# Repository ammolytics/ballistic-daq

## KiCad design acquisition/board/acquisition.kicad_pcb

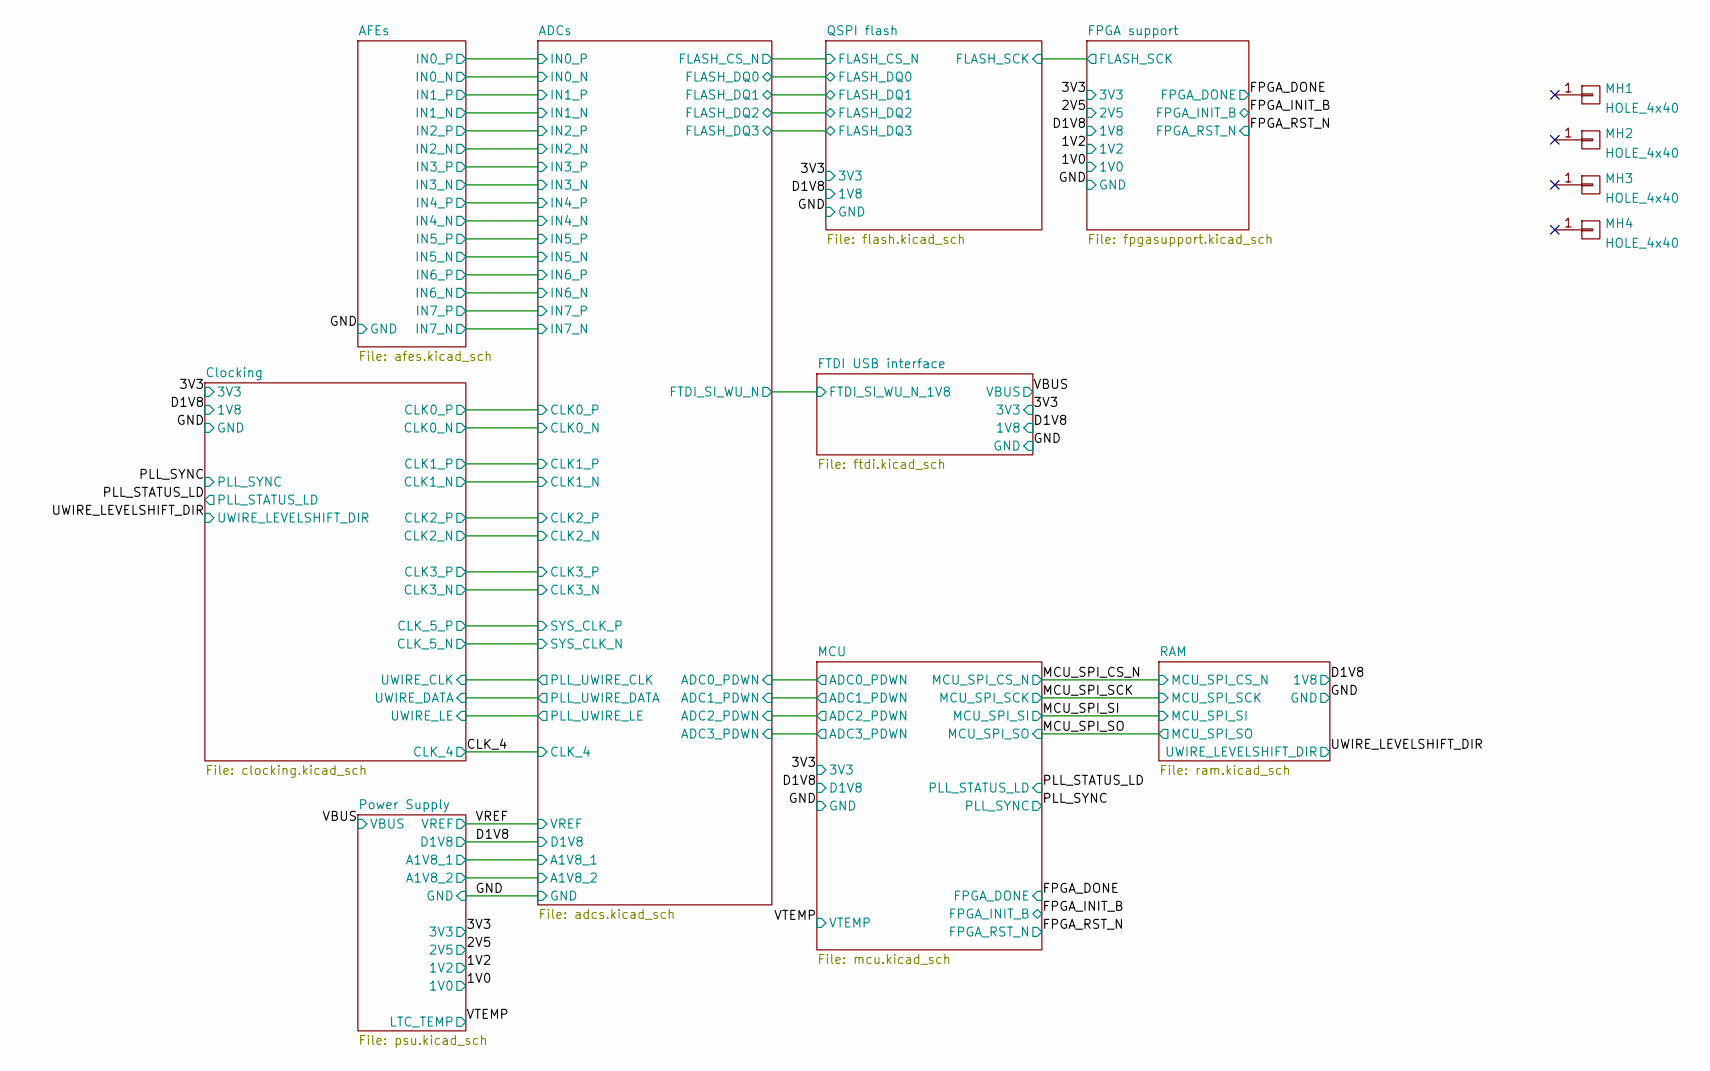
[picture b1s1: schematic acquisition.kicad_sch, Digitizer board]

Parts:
MH1, MH2, MH3, MH4: HOLE_4x40; MECHANICAL_CLEARANCEHOLE_4_40

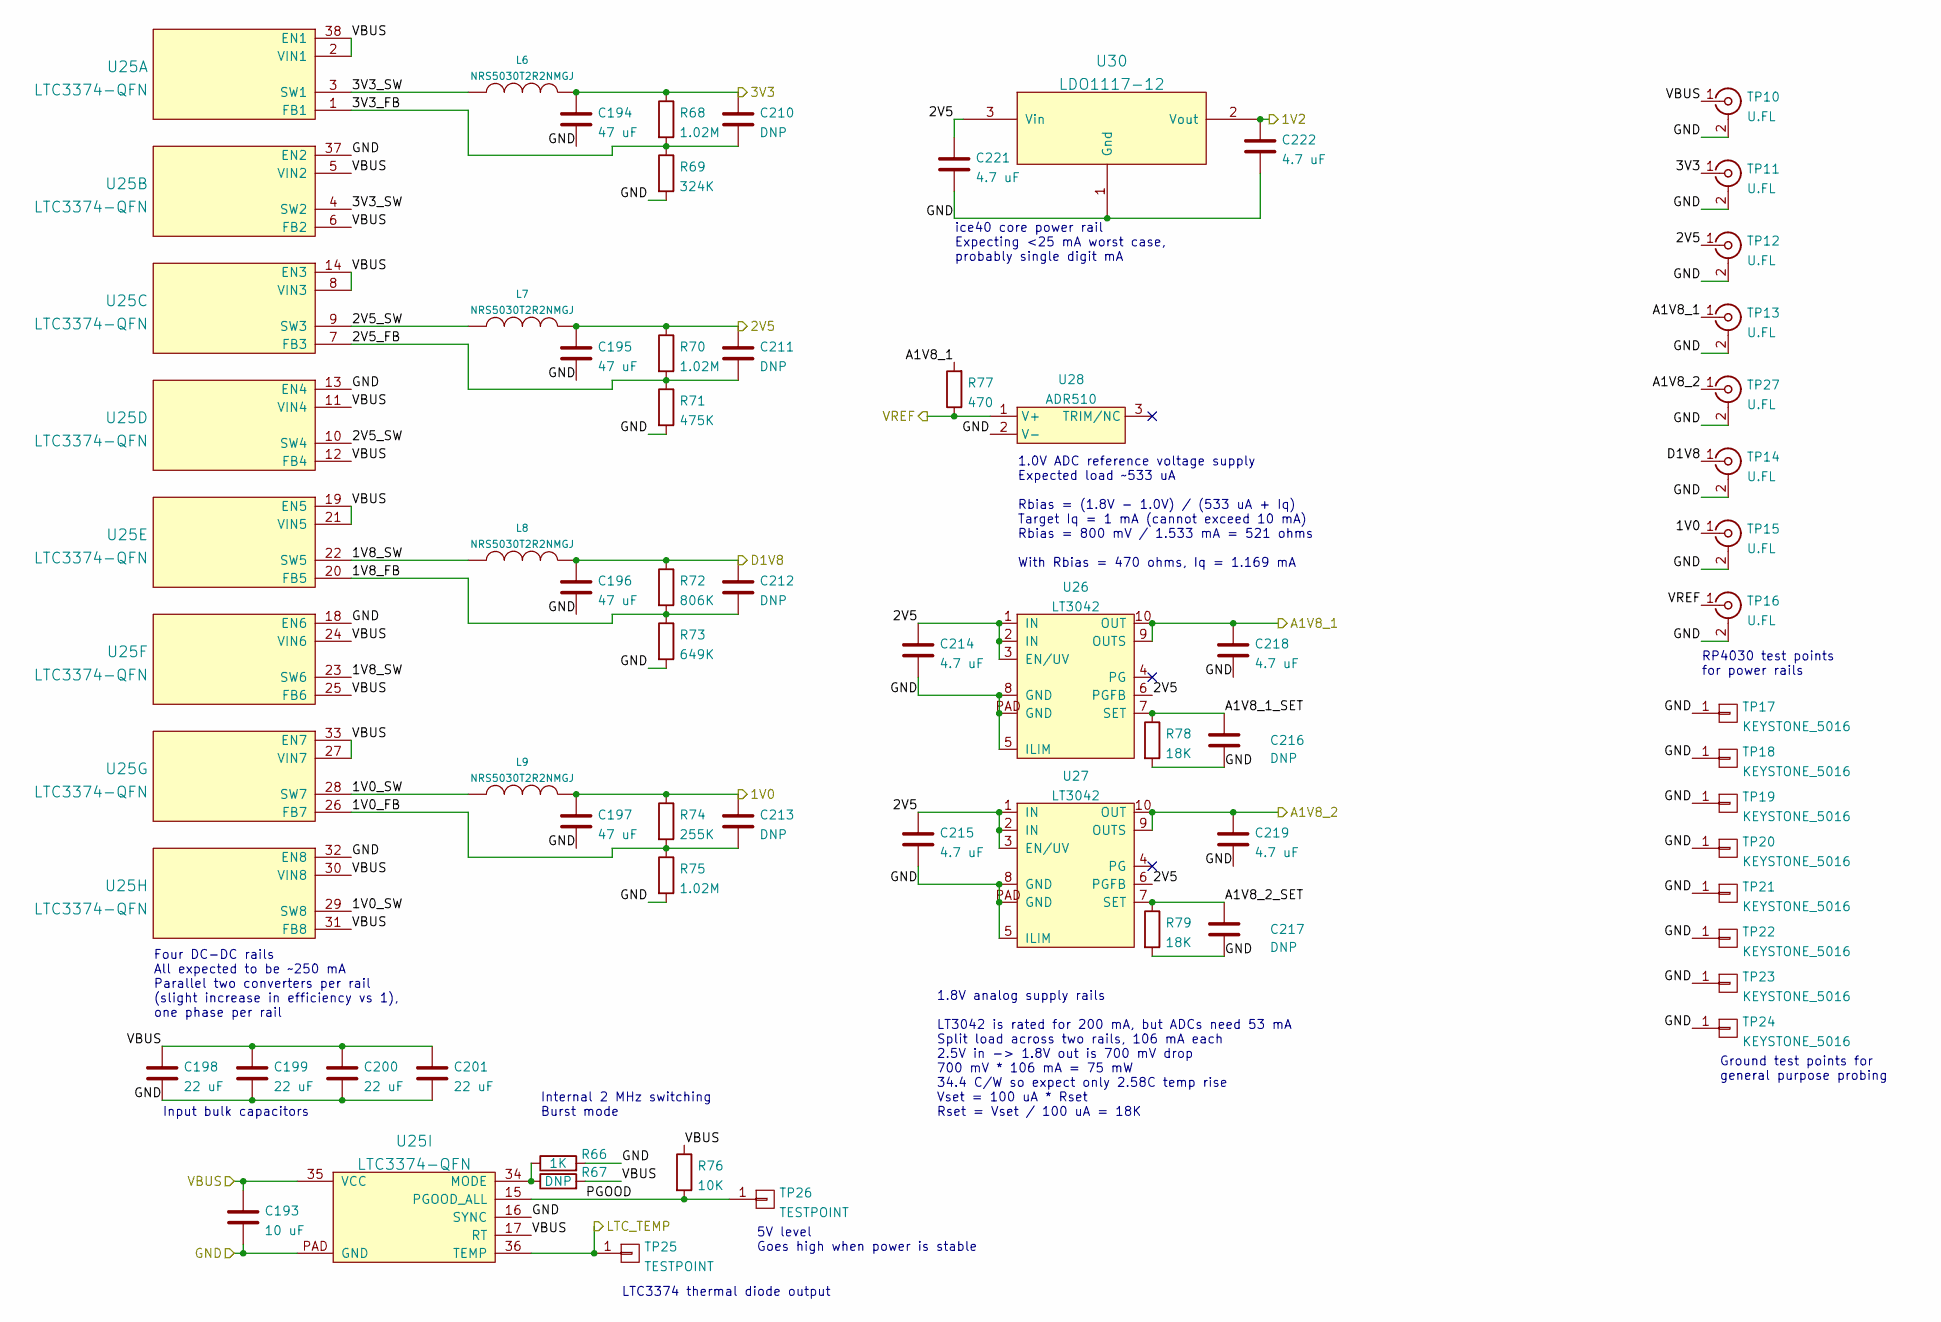
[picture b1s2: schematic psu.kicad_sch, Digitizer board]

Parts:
C193: 10 uF; EIA_1206_CAP_NOSILK
C194, C195, C196, C197: 47 uF; EIA_1206_CAP_NOSILK
C198, C199, C200, C201: 22 uF; EIA_1210_CAP_NOSILK
C210, C211, C212, C213, C216, C217: DNP; EIA_0402_CAP_NOSILK
C214, C215, C218, C219, C221, C222: 4.7 uF; EIA_0603_CAP_NOSILK
L6, L7, L8, L9: NRS5030T2R2NMGJ; INDUCTOR_YUDEN_NRS5030
R66: 1K; EIA_0402_RES_NOSILK
R67: DNP; EIA_0402_RES_NOSILK
R68, R70, R75: 1.02M; EIA_0402_RES_NOSILK
R69: 324K; EIA_0402_RES_NOSILK
R71: 475K; EIA_0402_RES_NOSILK
R72: 806K; EIA_0402_RES_NOSILK
R73: 649K; EIA_0402_RES_NOSILK
R74: 255K; EIA_0402_RES_NOSILK
R76: 10K; EIA_0402_RES_NOSILK
R77: 470; EIA_0402_RES_NOSILK
R78, R79: 18K; EIA_0402_RES_NOSILK
TP10, TP11, TP12, TP13, TP14, TP15, TP16, TP27: U.FL; CONN_U.FL_TE_1909763-1
TP17, TP18, TP19, TP20, TP21, TP22, TP23, TP24: KEYSTONE_5016; TESTPOINT_SMT_KEYSTONE_5016
TP25, TP26: TESTPOINT; TESTPOINT_SMT_0.5MM
U25: LTC3374-QFN; QFN_38_0.5MM_5x7MM
U26, U27: LT3042; DFN_10_0.5MM_3x3MM
U28: ADR510; SOT23_3
U30: LDO1117-12; SOT223-4

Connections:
/1V0: C197.1, C213.1, L9.1, R74.1, TP15.1 (In); also elsewhere on the board
/1V2: C222.1, U30.2 (Vout); also elsewhere on the board
/2V5: C195.1, C211.1, C214.1, C215.1, C221.1, L7.1, R70.1, TP12.1 (In), U26.1 (IN), U26.2 (IN), U26.3 (EN/UV), U26.6 (PGFB), U27.1 (IN), U27.2 (IN), U27.3 (EN/UV), U27.6 (PGFB), U30.3 (Vin); also elsewhere on the board
/3V3: C194.1, C210.1, L6.1, R68.1, TP11.1 (In); also elsewhere on the board
/ADCs/A1V8_1: C218.1, R77.2, TP13.1 (In), U26.9 (OUTS), U26.10 (OUT); also elsewhere on the board
/ADCs/A1V8_2: C219.1, TP27.1 (In), U27.9 (OUTS), U27.10 (OUT); also elsewhere on the board
/D1V8: C196.1, C212.1, L8.1, R72.1, TP14.1 (In); also elsewhere on the board
/GND: C193.2, C194.2, C195.2, C196.2, C197.2, C198.2, C199.2, C200.2, C201.2, C214.2, C215.2, C216.2, C217.2, C218.2, C219.2, C221.2, C222.2, R66.2, R69.2, R71.2, R73.2, R75.2, R78.2, R79.2, TP10.2 (Ext), TP11.2 (Ext), TP12.2 (Ext), TP13.2 (Ext), TP14.2 (Ext), TP15.2 (Ext), TP16.2 (Ext), TP17.1, TP18.1, TP19.1, TP20.1, TP21.1, TP22.1, TP23.1, TP24.1, TP27.2 (Ext), U25.13 (EN4), U25.16 (SYNC), U25.18 (EN6), U25.32 (EN8), U25.37 (EN2), U25.PAD (GND), U26.5 (ILIM), U26.8 (GND), U26.PAD (GND), U27.5 (ILIM), U27.8 (GND), U27.PAD (GND), U28.2 (V-), U30.1 (Gnd); also elsewhere on the board
/Power Supply/1V0_FB: C213.2, R74.2, R75.1, U25.26 (FB7)
/Power Supply/1V0_SW: L9.2, U25.28 (SW7), U25.29 (SW8)
/Power Supply/1V8_FB: C212.2, R72.2, R73.1, U25.20 (FB5)
/Power Supply/1V8_SW: L8.2, U25.22 (SW5), U25.23 (SW6)
/Power Supply/2V5_FB: C211.2, R70.2, R71.1, U25.7 (FB3)
/Power Supply/2V5_SW: L7.2, U25.9 (SW3), U25.10 (SW4)
/Power Supply/3V3_FB: C210.2, R68.2, R69.1, U25.1 (FB1)
/Power Supply/3V3_SW: L6.2, U25.3 (SW1), U25.4 (SW2)
/Power Supply/A1V8_1_SET: C216.1, R78.1, U26.7 (SET)
/Power Supply/A1V8_2_SET: C217.1, R79.1, U27.7 (SET)
/Power Supply/PGOOD: R76.2, TP26.1, U25.15 (PGOOD_ALL)
/VBUS: C193.1, C198.1, C199.1, C200.1, C201.1, R67.2, R76.1, TP10.1 (In), U25.2 (VIN1), U25.5 (VIN2), U25.6 (FB2), U25.8 (VIN3), U25.11 (VIN4), U25.12 (FB4), U25.14 (EN3), U25.17 (RT), U25.19 (EN5), U25.21 (VIN5), U25.24 (VIN6), U25.25 (FB6), U25.27 (VIN7), U25.30 (VIN8), U25.31 (FB8), U25.33 (EN7), U25.35 (VCC), U25.38 (EN1); also elsewhere on the board
/VREF: R77.1, TP16.1 (In), U28.1 (V+); also elsewhere on the board
/VTEMP: TP25.1, U25.36 (TEMP); also elsewhere on the board
unnamed: R66.1, R67.1, U25.34 (MODE)

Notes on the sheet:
ice40 core power rail Expecting <25 mA worst case, probably single digit mA
LTC3374 thermal diode output
Ground test points for general purpose probing
5V level Goes high when power is stable
Input bulk capacitors
1.8V analog supply rails LT3042 is rated for 200 mA, but ADCs need 53 mA Split load across two rails, 106 mA each 2.5V in -> 1.8V out is 700 mV drop 700 mV * 106 mA = 75 mW 34.4 C/W so expect only 2.58C temp rise Vset = 100 uA * Rset Rset = Vset / 100 uA = 18K
Internal 2 MHz switching Burst mode
RP4030 test points for power rails
Four DC-DC rails All expected to be ~250 mA Parallel two converters per rail (slight increase in efficiency vs 1), one phase per rail
1.0V ADC reference voltage supply Expected load ~533 uA Rbias = (1.8V - 1.0V) / (533 uA + Iq) Target Iq = 1 mA (cannot exceed 10 mA) Rbias = 800 mV / 1.533 mA = 521 ohms With Rbias = 470 ohms, Iq = 1.169 mA

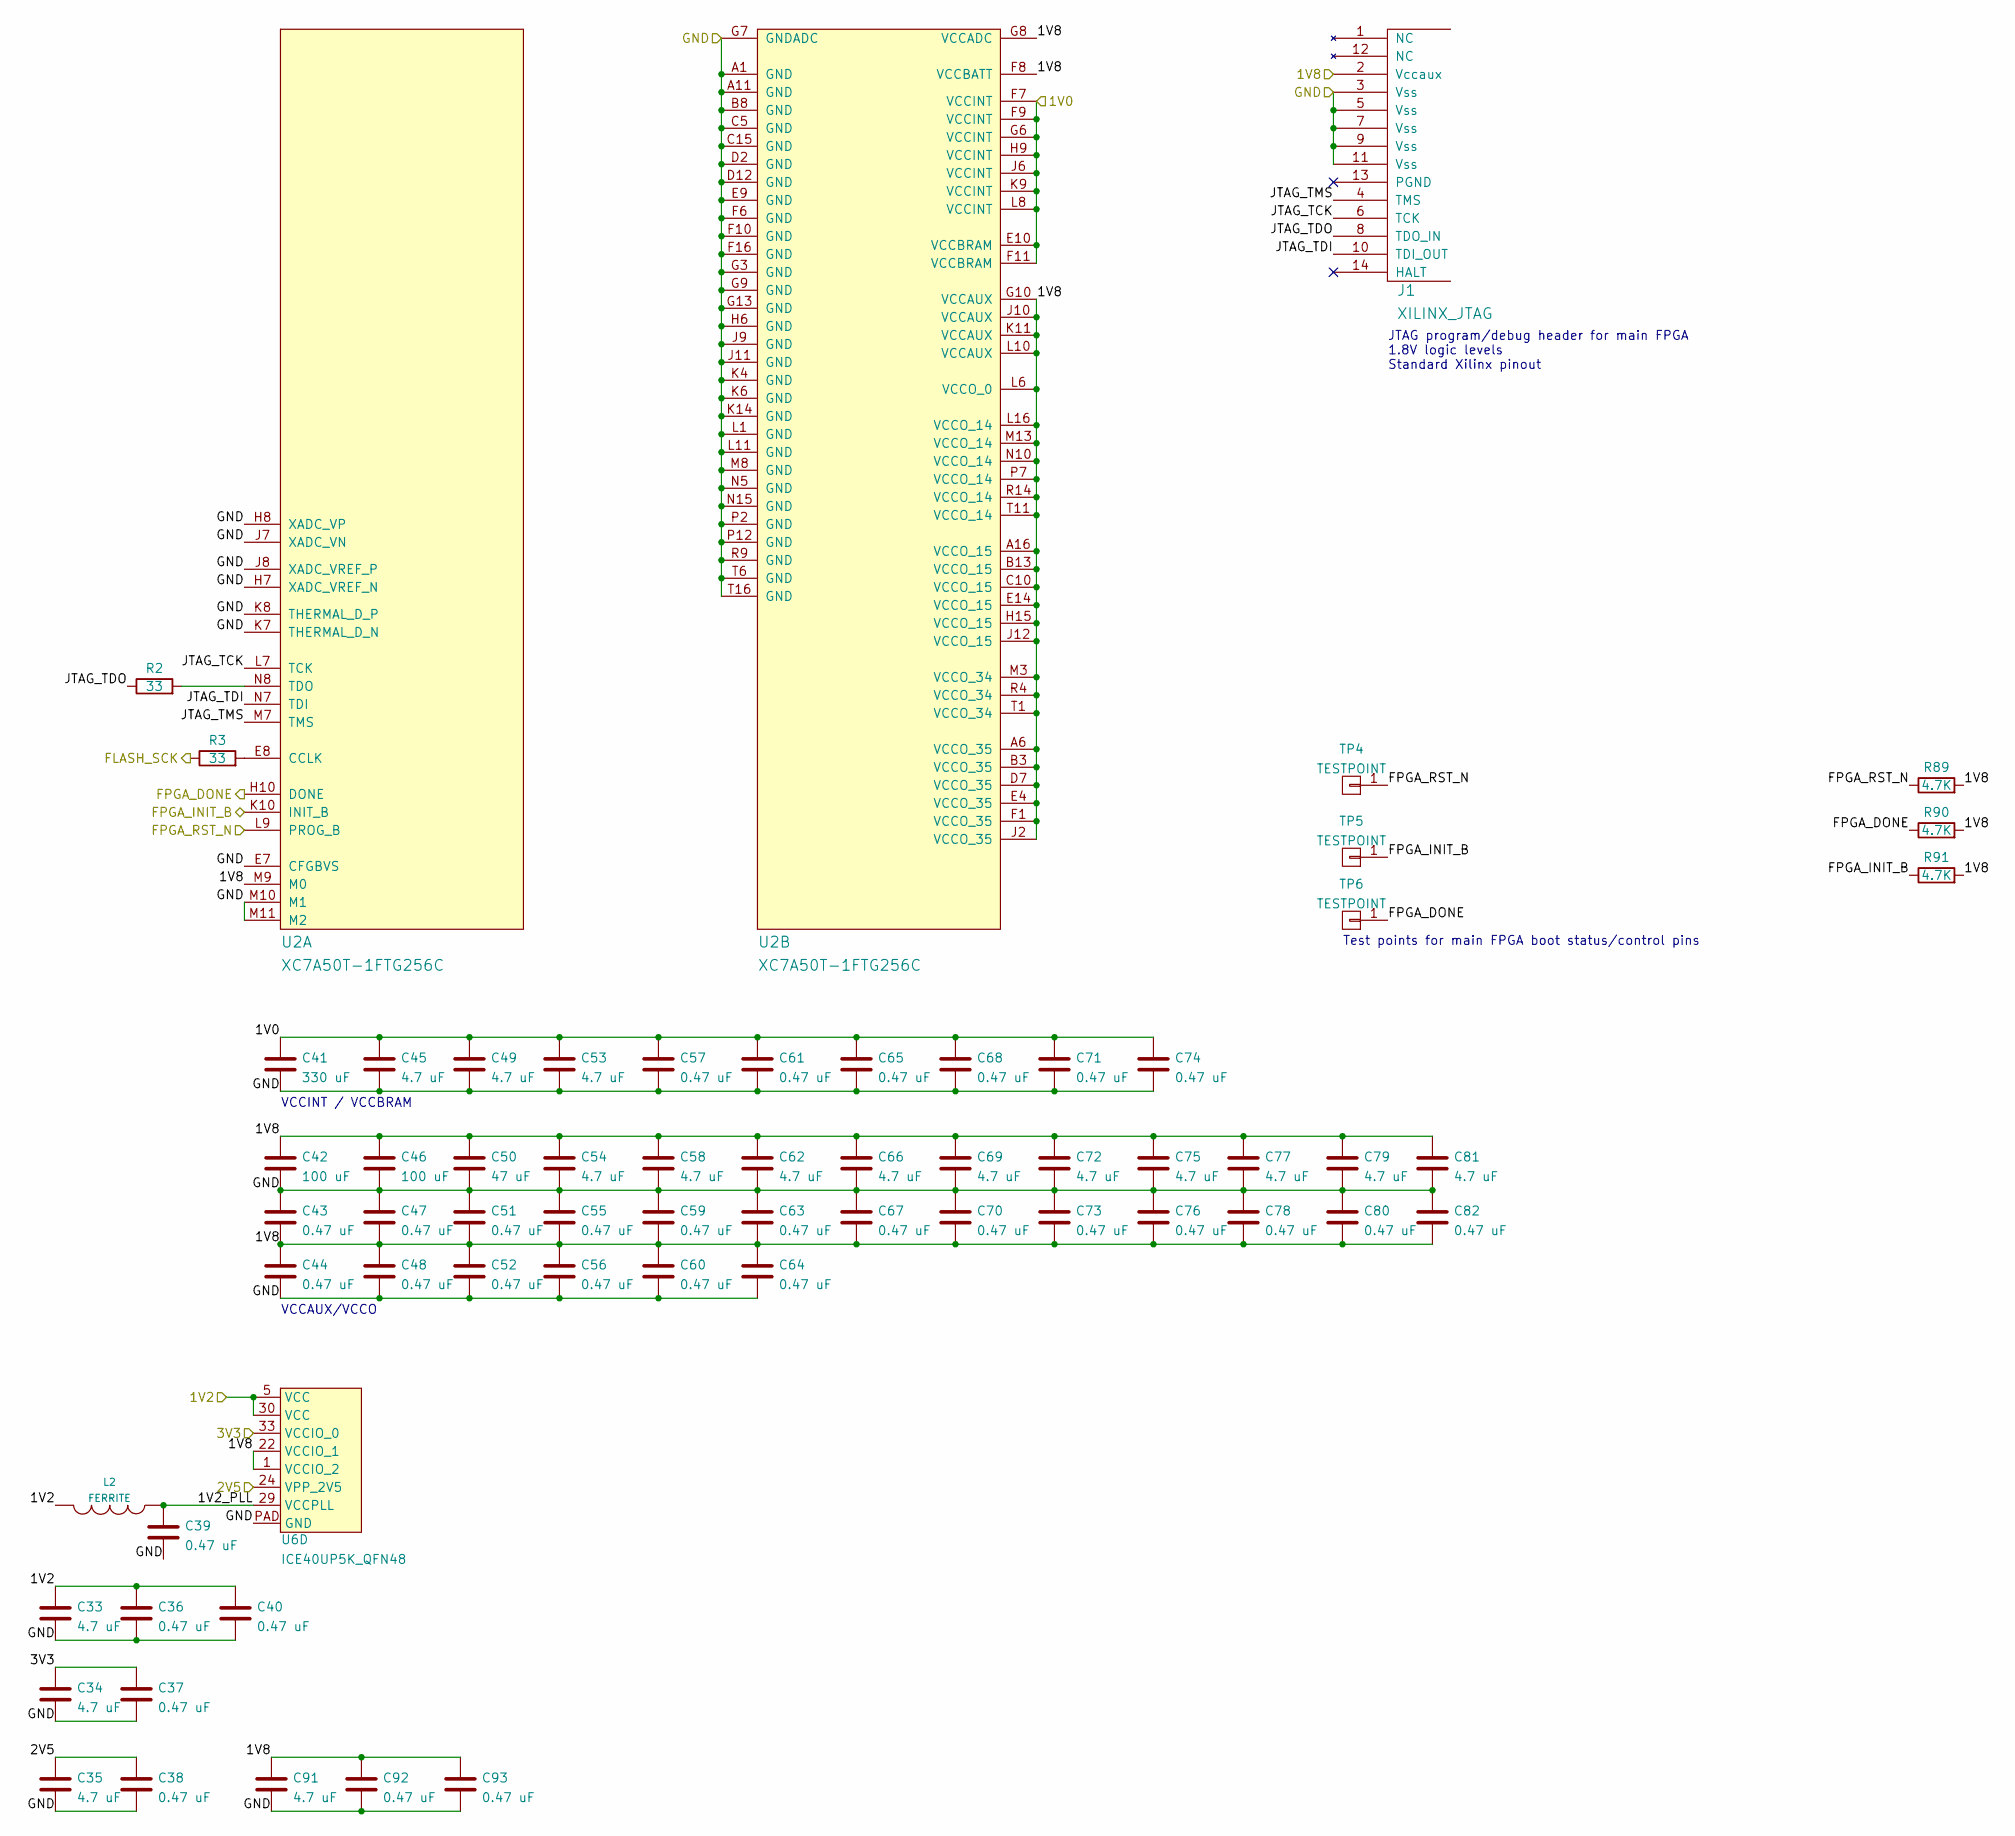
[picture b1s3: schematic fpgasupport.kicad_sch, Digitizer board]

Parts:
C33, C34, C35, C45, C49, C53, C54, C58, C62, C66, C69, C72, C75, C77, C79, C81, C91: 4.7 uF; EIA_0603_CAP_NOSILK
C36, C37, C38, C39, C40, C43, C44, C47, C48, C51, C52, C55, C56, C57, C59, C60, C61, C63, C64, C65, C67, C68, C70, C71, C73, C74, C76, C78, C80, C82, C92, C93: 0.47 uF; EIA_0402_CAP_NOSILK
C41: 330 uF; EIA_1210_CAP_NOSILK
C42, C46: 100 uF; EIA_1206_CAP_NOSILK
C50: 47 uF; EIA_1210_CAP_NOSILK
J1: XILINX_JTAG; XILINX_JTAG_PTH_MOLEX_0878311420
L2: FERRITE; EIA_0603_INDUCTOR_NOSILK
R2, R3: 33; EIA_0402_RES_NOSILK
R89, R90, R91: 4.7K; EIA_0402_RES_NOSILK
TP4, TP5, TP6: TESTPOINT; TESTPOINT_SMT_0.5MM
U2: XC7A50T-1FTG256C; BGA_256_17x17_FULLARRAY_1MM_0.4MM_FTG256
U6: ICE40UP5K_QFN48; QFN_48_0.5MM_7x7MM

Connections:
/1V0: C41.1, C45.1, C49.1, C53.1, C57.1, C61.1, C65.1, C68.1, C71.1, C74.1, U2.E10 (VCCBRAM), U2.F7 (VCCINT), U2.F9 (VCCINT), U2.F11 (VCCBRAM), U2.G6 (VCCINT), U2.H9 (VCCINT), U2.J6 (VCCINT), U2.K9 (VCCINT), U2.L8 (VCCINT); also elsewhere on the board
/1V2: C33.1, C36.1, C40.1, L2.2, U6.5 (VCC), U6.30 (VCC); also elsewhere on the board
/2V5: C35.1, C38.1, U6.24 (VPP_2V5); also elsewhere on the board
/3V3: C34.1, C37.1, U6.33 (VCCIO_0); also elsewhere on the board
/D1V8: C42.1, C43.2, C44.1, C46.1, C47.2, C48.1, C50.1, C51.2, C52.1, C54.1, C55.2, C56.1, C58.1, C59.2, C60.1, C62.1, C63.2, C64.1, C66.1, C67.2, C69.1, C70.2, C72.1, C73.2, C75.1, C76.2, C77.1, C78.2, C79.1, C80.2, C81.1, C82.2, C91.1, C92.1, C93.1, J1.2 (Vccaux), R89.2, R90.2, R91.2, U2.A6 (VCCO_35), U2.A16 (VCCO_15), U2.B3 (VCCO_35), U2.B13 (VCCO_15), U2.C10 (VCCO_15), U2.D7 (VCCO_35), U2.E4 (VCCO_35), U2.E14 (VCCO_15), U2.F1 (VCCO_35), U2.F8 (VCCBATT), U2.G8 (VCCADC), U2.G10 (VCCAUX), U2.H15 (VCCO_15), U2.J2 (VCCO_35), U2.J10 (VCCAUX), U2.J12 (VCCO_15), U2.K11 (VCCAUX), U2.L6 (VCCO_0), U2.L10 (VCCAUX), U2.L16 (VCCO_14), U2.M3 (VCCO_34), U2.M9 (M0), U2.M13 (VCCO_14), U2.N10 (VCCO_14), U2.P7 (VCCO_14), U2.R4 (VCCO_34), U2.R14 (VCCO_14), U2.T1 (VCCO_34), U2.T11 (VCCO_14), U6.1 (VCCIO_2), U6.22 (VCCIO_1); also elsewhere on the board
/FPGA support/1V2_PLL: C39.1, L2.1, U6.29 (VCCPLL)
/FPGA support/FLASH_SCK: R3.1; also elsewhere on the board
/FPGA support/JTAG_TCK: J1.6 (TCK), U2.L7 (TCK)
/FPGA support/JTAG_TDI: J1.10 (TDI_OUT), U2.N7 (TDI)
/FPGA support/JTAG_TDO: J1.8 (TDO_IN), R2.1
/FPGA support/JTAG_TMS: J1.4 (TMS), U2.M7 (TMS)
/FPGA_DONE: R90.1, TP6.1, U2.H10 (DONE); also elsewhere on the board
/FPGA_INIT_B: R91.1, TP5.1, U2.K10 (INIT_B); also elsewhere on the board
/FPGA_RST_N: R89.1, TP4.1, U2.L9 (PROG_B); also elsewhere on the board
/GND: C33.2, C34.2, C35.2, C36.2, C37.2, C38.2, C39.2, C40.2, C41.2, C42.2, C43.1, C44.2, C45.2, C46.2, C47.1, C48.2, C49.2, C50.2, C51.1, C52.2, C53.2, C54.2, C55.1, C56.2, C57.2, C58.2, C59.1, C60.2, C61.2, C62.2, C63.1, C64.2, C65.2, C66.2, C67.1, C68.2, C69.2, C70.1, C71.2, C72.2, C73.1, C74.2, C75.2, C76.1, C77.2, C78.1, C79.2, C80.1, C81.2, C82.1, C91.2, C92.2, C93.2, J1.3 (Vss), J1.5 (Vss), J1.7 (Vss), J1.9 (Vss), J1.11 (Vss), U2.A1 (GND), U2.A11 (GND), U2.B8 (GND), U2.C5 (GND), U2.C15 (GND), U2.D2 (GND), U2.D12 (GND), U2.E7 (CFGBVS), U2.E9 (GND), U2.F6 (GND), U2.F10 (GND), U2.F16 (GND), U2.G3 (GND), U2.G7 (GNDADC), U2.G9 (GND), U2.G13 (GND), U2.H6 (GND), U2.H7 (XADC_VREF_N), U2.H8 (XADC_VP), U2.J7 (XADC_VN), U2.J8 (XADC_VREF_P), U2.J9 (GND), U2.J11 (GND), U2.K4 (GND), U2.K6 (GND), U2.K7 (THERMAL_D_N), U2.K8 (THERMAL_D_P), U2.K14 (GND), U2.L1 (GND), U2.L11 (GND), U2.M8 (GND), U2.M10 (M1), U2.M11 (M2), U2.N5 (GND), U2.N15 (GND), U2.P2 (GND), U2.P12 (GND), U2.R9 (GND), U2.T6 (GND), U2.T16 (GND), U6.PAD (GND); also elsewhere on the board
unnamed: R2.2, U2.N8 (TDO)
unnamed: R3.2, U2.E8 (CCLK)

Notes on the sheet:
JTAG program/debug header for main FPGA 1.8V logic levels Standard Xilinx pinout
Test points for main FPGA boot status/control pins
VCCINT / VCCBRAM
VCCAUX/VCCO

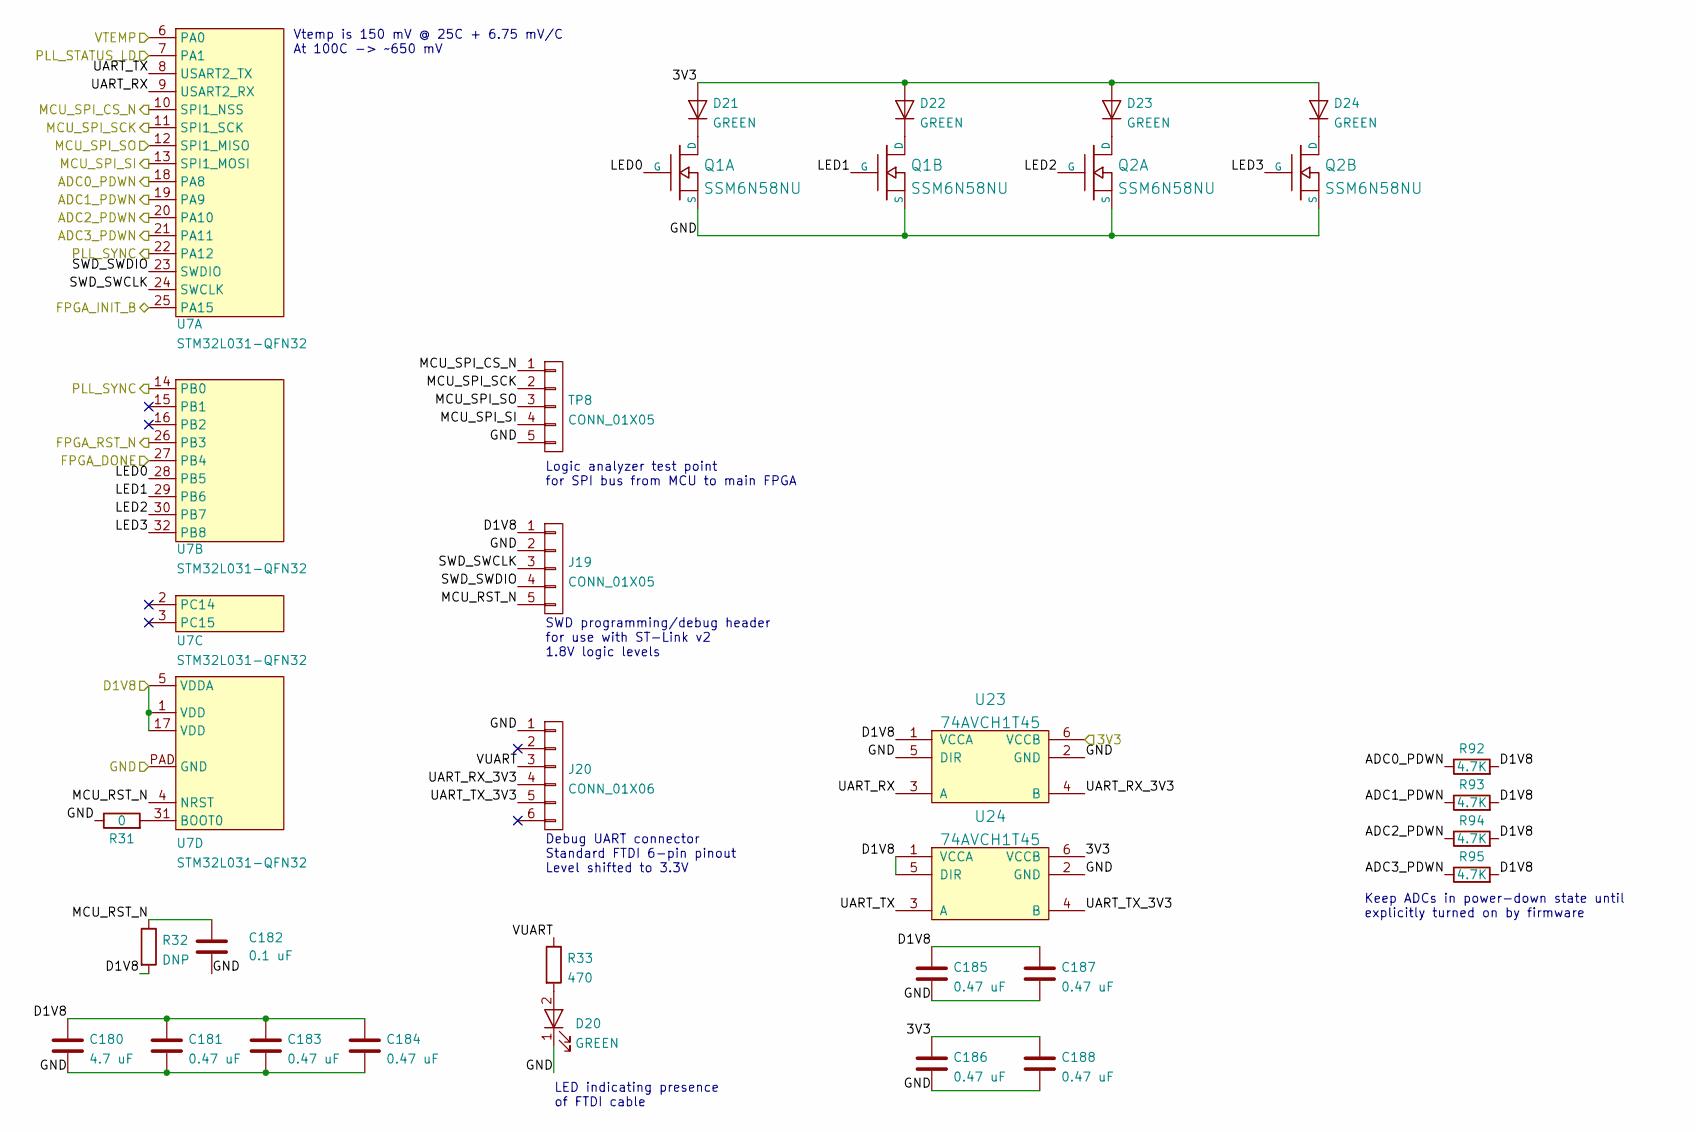
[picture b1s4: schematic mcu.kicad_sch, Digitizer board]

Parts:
C180: 4.7 uF; EIA_0603_CAP_NOSILK
C181, C183, C184, C185, C186, C187, C188: 0.47 uF; EIA_0402_CAP_NOSILK
C182: 0.1 uF; EIA_0402_CAP_NOSILK
D20, D21, D22, D23, D24: GREEN; EIA_0603_LED
J19: CONN_01X05; CONN_HEADER_2.54MM_1x5
J20: CONN_01X06; CONN_HEADER_2.54MM_1x6
Q1, Q2: SSM6N58NU; DFN_6_0.65MM_2x2MM_GDS
R31: 0; EIA_0402_RES_NOSILK
R32: DNP; EIA_0402_RES_NOSILK
R33: 470; EIA_0402_RES_NOSILK
R92, R93, R94, R95: 4.7K; EIA_0402_RES_NOSILK
TP8: CONN_01X05; CONN_HEADER_2.54MM_1x5
U7: STM32L031-QFN32; QFN_32_0.5MM_5x5MM
U23, U24: 74AVCH1T45; DFN_6_0.5MM_1.45x1.00MM

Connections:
/3V3: C186.1, C188.1, D21.2 (A), D22.2 (A), D23.2 (A), D24.2 (A), U23.6 (VCCB), U24.6 (VCCB); also elsewhere on the board
/D1V8: C180.1, C181.1, C183.1, C184.1, C185.1, C187.1, J19.1, R32.2, R92.2, R93.2, R94.2, R95.2, U7.1 (VDD), U7.5 (VDDA), U7.17 (VDD), U23.1 (VCCA), U24.1 (VCCA), U24.5 (DIR); also elsewhere on the board
/FPGA_DONE: U7.27 (PB4); also elsewhere on the board
/FPGA_INIT_B: U7.25 (PA15); also elsewhere on the board
/FPGA_RST_N: U7.26 (PB3); also elsewhere on the board
/GND: C180.2, C181.2, C182.2, C183.2, C184.2, C185.2, C186.2, C187.2, C188.2, D20.1 (K), J19.2, J20.1, Q1.S1 (S), Q1.S2 (S), Q2.S1 (S), Q2.S2 (S), R31.1, TP8.5, U7.PAD (GND), U23.2 (GND), U23.5 (DIR), U24.2 (GND); also elsewhere on the board
/MCU/ADC0_PDWN: R92.1, U7.18 (PA8); also elsewhere on the board
/MCU/ADC1_PDWN: R93.1, U7.19 (PA9); also elsewhere on the board
/MCU/ADC2_PDWN: R94.1, U7.20 (PA10); also elsewhere on the board
/MCU/ADC3_PDWN: R95.1, U7.21 (PA11); also elsewhere on the board
/MCU/LED0: Q1.G1 (G), U7.28 (PB5)
/MCU/LED1: Q1.G2 (G), U7.29 (PB6)
/MCU/LED2: Q2.G1 (G), U7.30 (PB7)
/MCU/LED3: Q2.G2 (G), U7.32 (PB8)
/MCU/MCU_RST_N: C182.1, J19.5, R32.1, U7.4 (NRST)
/MCU/SWD_SWCLK: J19.3, U7.24 (SWCLK)
/MCU/SWD_SWDIO: J19.4, U7.23 (SWDIO)
/MCU/UART_RX: U7.9 (USART2_RX), U23.3 (A)
/MCU/UART_RX_3V3: J20.4, U23.4 (B)
/MCU/UART_TX: U7.8 (USART2_TX), U24.3 (A)
/MCU/UART_TX_3V3: J20.5, U24.4 (B)
/MCU/VUART: J20.3, R33.1
/MCU_SPI_CS_N: TP8.1, U7.10 (SPI1_NSS); also elsewhere on the board
/MCU_SPI_SCK: TP8.2, U7.11 (SPI1_SCK); also elsewhere on the board
/MCU_SPI_SI: TP8.4, U7.13 (SPI1_MOSI); also elsewhere on the board
/MCU_SPI_SO: TP8.3, U7.12 (SPI1_MISO); also elsewhere on the board
/PLL_STATUS_LD: U7.7 (PA1); also elsewhere on the board
/PLL_SYNC: U7.14 (PB0), U7.22 (PA12); also elsewhere on the board
/VTEMP: U7.6 (PA0); also elsewhere on the board
unnamed: D20.2 (A), R33.2
unnamed: D21.1 (K), Q1.D1 (D)
unnamed: D22.1 (K), Q1.D2 (D)
unnamed: D23.1 (K), Q2.D1 (D)
unnamed: D24.1 (K), Q2.D2 (D)
unnamed: R31.2, U7.31 (BOOT0)

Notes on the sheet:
Keep ADCs in power-down state until explicitly turned on by firmware
SWD programming/debug header for use with ST-Link v2 1.8V logic levels
Debug UART connector Standard FTDI 6-pin pinout Level shifted to 3.3V
Logic analyzer test point for SPI bus from MCU to main FPGA
LED indicating presence of FTDI cable
Vtemp is 150 mV @ 25C + 6.75 mV/C At 100C -> ~650 mV
